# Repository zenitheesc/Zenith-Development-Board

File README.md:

<h1 align="center" style="color:white; background-color:black">Zenith Development Board</h1>
<h4 align="center">A Development Board based on STM32F103C8T6</h4>

<p align="center">

</p>

<p align="center">
    <a href="#environment-and-tools">Environment and Tools</a> •
    <a href="#how-to-contribute">How to contribute?</a> 
</p>

## Environment and tools

This board was developed using [KiCad](https://www.kicad.org/) with native components.

## How to contribute

Fork your personal Git and add your hardware and software version in the "Development" folder following the Issues listed in the repository.

---

<p align="center">

</p>
<p align = "center">
<a href="zenith.eesc@gmail.com">zenith.eesc@gmail.com</a>
</p>

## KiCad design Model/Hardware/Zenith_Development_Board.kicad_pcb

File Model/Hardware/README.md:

# Zenith Development Board

Development board based on the STM32F103C8T6 developed to introduce the group members to circuits similar to those that can be used in the projects, including light, acceleration, rotation, pressure and temperature sensors, as well as actuators such as Mosfets, Relays and Leds.

# Schematic

# Layout

# B.O.M.
|Component|Amount|Description|
|--|--|--|
|STM32F103C8T6|1|Microcontroller|
|Crystal|1|16MHz|
|MPU-6050|1|Accelerometer and Gyroscope|
|BMP280|1|Pressure and temperature sensor|
|LDR|1|Light Dependent Resistor|
|RGB-LED|1|Led SMD|
|Button|2|Push button|
|ESD suppressor|2|652-CGA0603MLC-12E|
|Micro USB|1|Micro USB connector|
|ESD Protection|1|USBLC6-4SC6Y|
|Linear regulator|1|LD1117S33TR|
|Rele|1|G5V-1-DC5|
|Mosfet|1|DMG1012T-7|

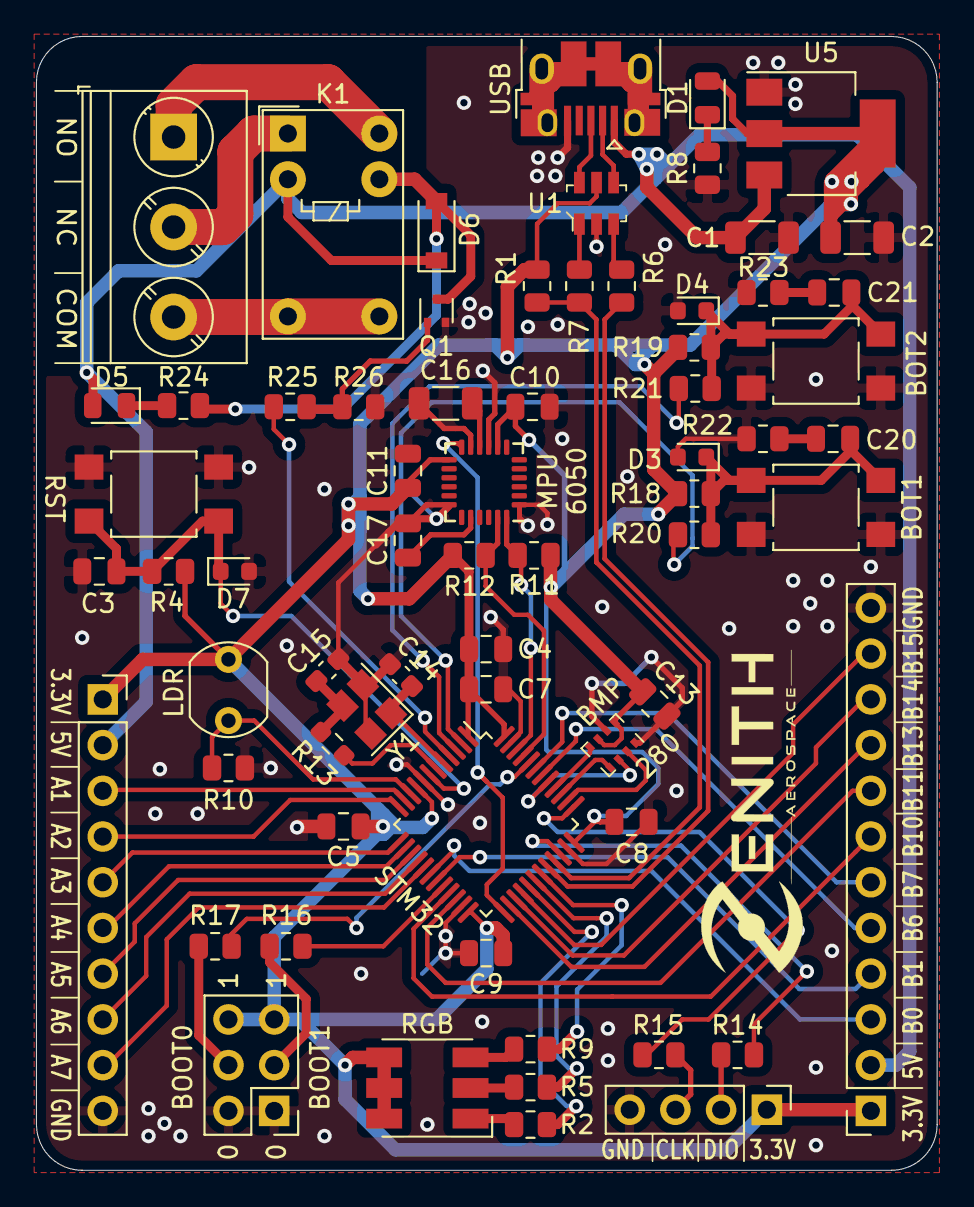
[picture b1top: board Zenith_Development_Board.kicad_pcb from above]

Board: 2 copper layers, 50.0 x 63.0 mm, 67 parts (0 on the bottom side), 67 nets.

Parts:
C1: 100nF; C_1206_3216Metric
C2: 10uF; C_1206_3216Metric
C3, C11, C13, C20, C21: 0.1uF; C_0805_2012Metric
C4: 4u7; C_0805_2012Metric
C5, C7, C8, C9: 100n; C_0805_2012Metric
C10: 10nF; C_0805_2012Metric
C14, C15: 30p; C_0603_1608Metric_Pad1.08x0.95mm_HandSolder
C16: 0.1uF; C_1206_3216Metric
C17: 2.2nF; C_0805_2012Metric
D1, D5: LED_Small; LED_0805_2012Metric
D2: LED_RGB; LED_RGB_5050-6
D3, D4, D7: TVS; D_0603_1608Metric
D6: BAS16GWX; D_SOD-123
J1: USB_B_Micro; USB_Micro-B_Amphenol_10103594-0001LF_Horizontal
J2: Conn_01x10_Female; PinSocket_1x10_P2.54mm_Vertical
J3: Screw_Terminal_01x03; TerminalBlock_Phoenix_PT-1,5-3-5.0-H_1x03_P5.00mm_Horizontal
J4: Conn_01x04_Male; PinHeader_1x04_P2.54mm_Vertical
J5: Conn_02x03_Odd_Even; PinHeader_2x03_P2.54mm_Vertical
J7: Conn_01x12_Female; PinSocket_1x12_P2.54mm_Vertical
K1: G5V-1; Relay_SPDT_Omron_G5V-1
Q1: DMG1012T; SOT-523
R1: 1.5K; R_0805_2012Metric
R2, R5, R9, R24: 330; R_0805_2012Metric
R3: LDR07; R_LDR_5.1x4.3mm_P3.4mm_Vertical
R4, R16, R17, R26: 10K; R_0805_2012Metric
R6, R7, R14, R15: 22; R_0805_2012Metric
R8, R22, R23: 100; R_0805_2012Metric
R10, R11, R12, R18, R19: 4.7K; R_0805_2012Metric
R13: 0; R_0603_1608Metric_Pad0.98x0.95mm_HandSolder
R20, R21: 220; R_0805_2012Metric
R25: 1K; R_0805_2012Metric
SW1, SW2, SW3: SW_Push; SW_SPST_TL3305A
U1: USBLC6-2P6; SOT23-6L
U2: MPU-6050; InvenSense_QFN-24_4x4mm_P0.5mm
U3: BMP280; Bosch_LGA-8_2x2.5mm_P0.65mm_ClockwisePinNumbering
U4: STM32F103C8T6; LQFP-48_7x7mm_P0.5mm
U5: LD1117S33TR_SOT223; SOT-223-3_TabPin2
Y1: Crystal_GND24; Crystal_SMD_SeikoEpson_FA238-4Pin_3.2x2.5mm

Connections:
+3V3: C2.1, C4.1, C5.1, C7.1, C8.1, C9.1, C10.2, C11.1, C13.1, D1.2, D2.4, D2.5, D2.6, J2.1, J4.1, J5.5, J5.6, J7.1, R1.2, R3.1, R4.1, R11.1, R12.1, R18.1, R19.1, U1.5, U2.8, U2.13, U3.6, U3.8, U4.1, U4.9, U4.24, U4.36, U4.48, U5.2
+5V: C1.1, D5.2, D6.1, J1.1, J2.2, J7.2, K1.2, U5.3
ACC_IT: U2.12, U4.25
ADC1_IN0: R3.2, R10.1, U4.10
BOOT0: R17.1, U4.44
BOOT1: R16.1, U4.20
BUTTON_1: R20.2, U4.2
BUTTON_2: R21.2, U4.3
GND: C1.2, C2.2, C3.1, C4.2, C5.2, C7.2, C8.2, C9.2, C10.1, C11.2, C13.2, C14.2, C15.2, C16.2, C17.2, D3.2, D4.2, D7.2, J1.5, J2.10, J4.4, J5.1, J5.2, J7.12, Q1.2, R8.1, R10.2, R22.2, R23.2, R26.2, SW1.2, SW2.2, SW3.2, U1.2, U2.1, U2.9, U2.11, U2.18, U3.1, U3.7, U4.8, U4.23, U4.35, U4.47, U5.1, Y1.2, Y1.4
HSE_IN: C14.1, U4.5, Y1.1
HSE_OUT: R13.2, U4.6
I2C1_SCL: R12.2, U2.23, U4.45
I2C1_SDA: R11.2, U2.24, U4.46
NRST: C3.2, D7.1, R4.2, SW1.1, U4.7
unnamed: C15.1, R13.1, Y1.3
unnamed: C16.1, U2.10
unnamed: C17.1, U2.20
unnamed: C20.1, R22.1
unnamed: C20.2, D3.1, R18.2, R20.1, SW2.1
unnamed: C21.1, R23.1
unnamed: C21.2, D4.1, R19.2, R21.1, SW3.1
unnamed: D1.1, R8.2
unnamed: D2.1, R2.1
unnamed: D2.2, R5.1
unnamed: D2.3, R9.1
unnamed: D5.1, R24.2
unnamed: D6.2, K1.9, Q1.3, R24.1
unnamed: J3.1, K1.10
unnamed: J3.2, K1.1
unnamed: J3.3, K1.5, K1.6
unnamed: J4.2, R14.1
unnamed: J4.3, R15.1
unnamed: J5.3, R16.2
unnamed: J5.4, R17.2
unnamed: Q1.1, R25.1, R26.1
unnamed: R6.1, U1.3
unnamed: R7.2, U1.1
PA1: J2.3, U4.11
PA2: J2.4, U4.12
PA3: J2.5, U4.13
PA4: J2.6, U4.14
PA5: J2.7, U4.15
PA6: J2.8, U4.16
PA7: J2.9, U4.17
PB0: J7.3, U4.18
PB1: J7.4, U4.19
PB6: J7.5, U4.42
PB7: J7.6, U4.43
PB10: J7.7, U4.21
PB11: J7.8, U4.22
PB13: J7.9, U4.26
PB14: J7.10, U4.27
PB15: J7.11, U4.28
PWM_B: R9.2, U4.31
PWM_G: R5.2, U4.30
PWM_R: R2.2, U4.29
RELAY: R25.2, U4.4
SPI1_MISO: U3.5, U4.40
SPI1_MOSI: U3.3, U4.41
SPI1_NSS: U3.2, U4.38
SPI1_SCK: U3.4, U4.39
SWCLK: R15.2, U4.37
SWDIO: R14.2, U4.34
USB_CONN_D+: J1.3, U1.6
USB_CONN_D-: J1.2, U1.4
USB_D+: R1.1, R7.1, U4.33
USB_D-: R6.2, U4.32
